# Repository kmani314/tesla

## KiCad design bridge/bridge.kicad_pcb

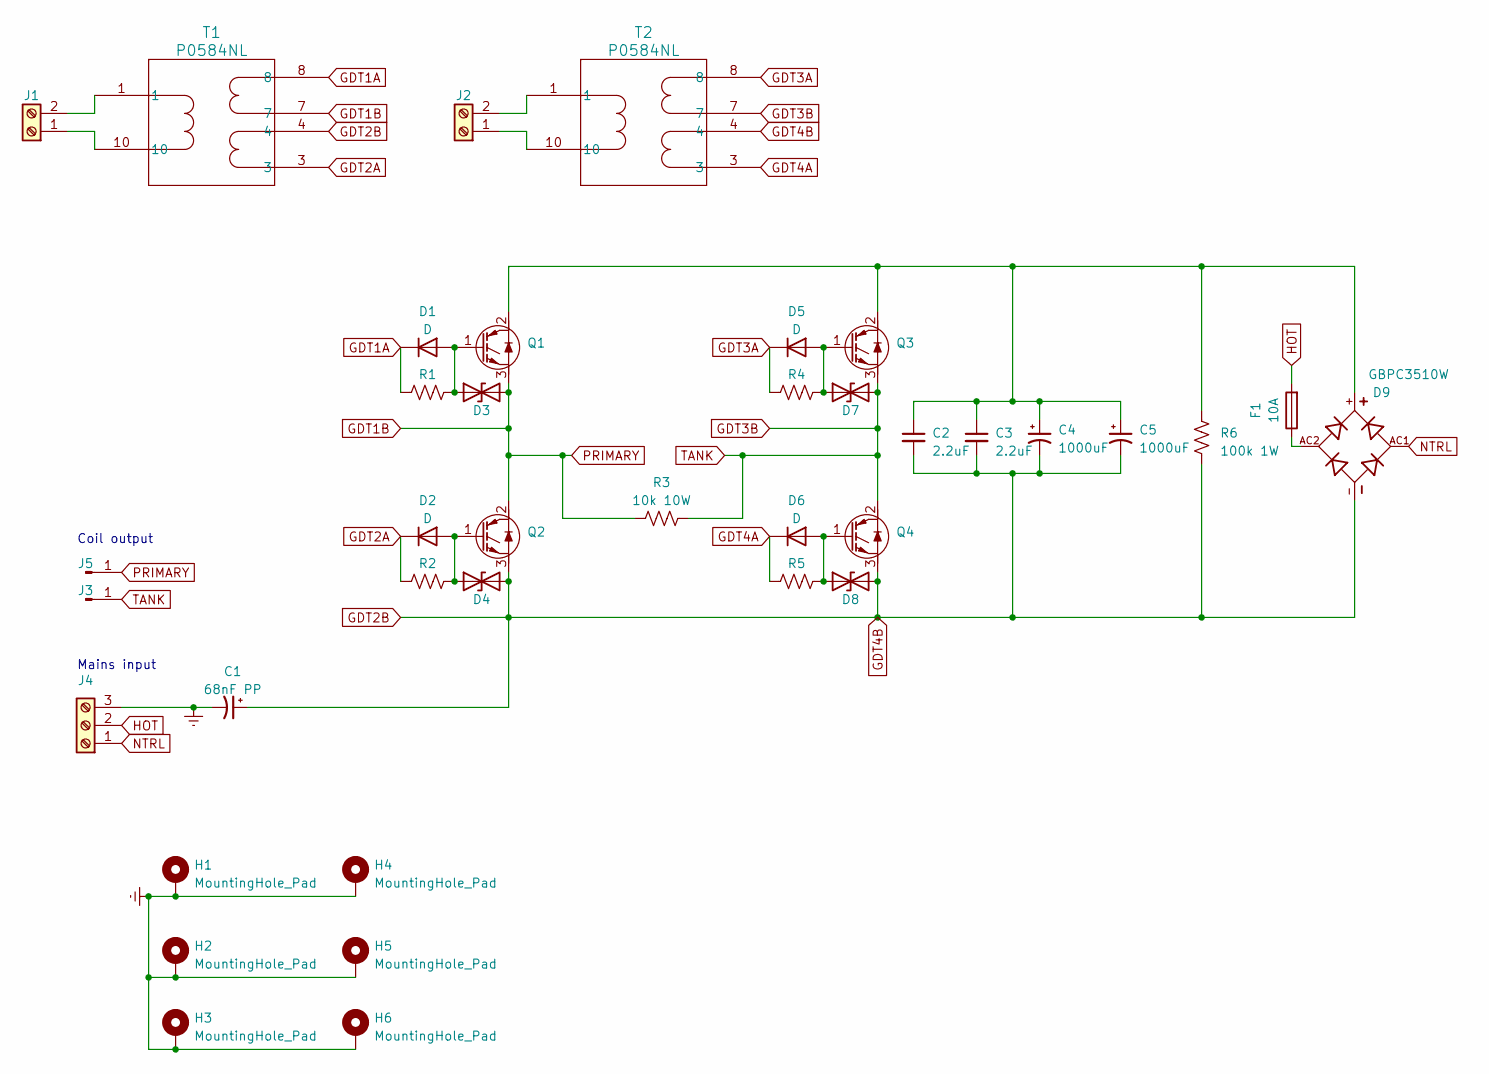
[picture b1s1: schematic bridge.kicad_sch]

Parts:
C1: 68nF PP; C_Rect_L18.0mm_W9.0mm_P15.00mm_FKS3_FKP3
C2, C3: 2.2uF; C_Rect_L26.5mm_W11.5mm_P22.50mm_MKS4
C4, C5: 1000uF; CP_Radial_D35.0mm_P10.00mm_SnapIn
D1, D2, D5, D6: D; D_SOD-123F
D3, D4, D7, D8: D_TVS; D_SMA
D9: GBPC3510W; DIOB_GBPC3510W; PARTREV L2103
F1: 10A; 696108003002
H1, H2, H3, H4, H5, H6: MountingHole_Pad; MountingHole_3.2mm_M3_Pad_Via
J1, J2: Screw_Terminal_01x02; PHOENIX_1935161
J3, J5: Conn_01x01_Pin; TE_1217861-1
J4: Screw_Terminal_01x03; PHOENIX_1935174
Q1, Q2, Q3, Q4: STGP7NC60HD; TO-3P-3_Horizontal_TabDown
R1, R2, R4, R5: R_US; R_1206_3216Metric_Pad1.30x1.75mm_HandSolder
R3: 10k 10W; R_Axial_Shunt_L22.2mm_W8.0mm_PS14.30mm_P25.40mm
R6: 100k 1W; R_Axial_DIN0207_L6.3mm_D2.5mm_P7.62mm_Horizontal
T1, T2: P0584NL; P0584NL_PUL

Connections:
Earth: C1.2, H1.1, H2.1, H3.1, H4.1, H5.1, H6.1, J4.3
GDT1A: D1.1 (K), R1.2, T1.8
GDT1B: D3.2 (A2), J5.1, Q1.3 (E), Q2.2 (C), R3.2, T1.7
GDT2A: D2.1 (K), R2.2, T1.3
GDT2B: C1.1, C2.2, C3.2, C4.2, C5.2, D4.2 (A2), D8.2 (A2), D9.-, Q2.3 (E), Q4.3 (E), R6.2, T1.4, T2.4
GDT3A: D5.1 (K), R4.2, T2.8
GDT3B: D7.2 (A2), J3.1, Q3.3 (E), Q4.2 (C), R3.1, T2.7
GDT4A: D6.1 (K), R5.2, T2.3
HOT: F1.2, J4.2
NTRL: D9.AC1, J4.1
unnamed: D1.2 (A), D3.1 (A1), Q1.1 (G), R1.1
unnamed: D2.2 (A), D4.1 (A1), Q2.1 (G), R2.1
unnamed: D5.2 (A), D7.1 (A1), Q3.1 (G), R4.1
unnamed: D6.2 (A), D8.1 (A1), Q4.1 (G), R5.1
unnamed: D9.AC2, F1.1
unnamed: J1.1, T1.10
unnamed: J1.2, T1.1
unnamed: J2.1, T2.10
unnamed: J2.2, T2.1
unnamed: C2.1, C3.1, C4.1, C5.1, D9.+, Q1.2 (C), Q3.2 (C), R6.1

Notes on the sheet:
Mains input
Coil output

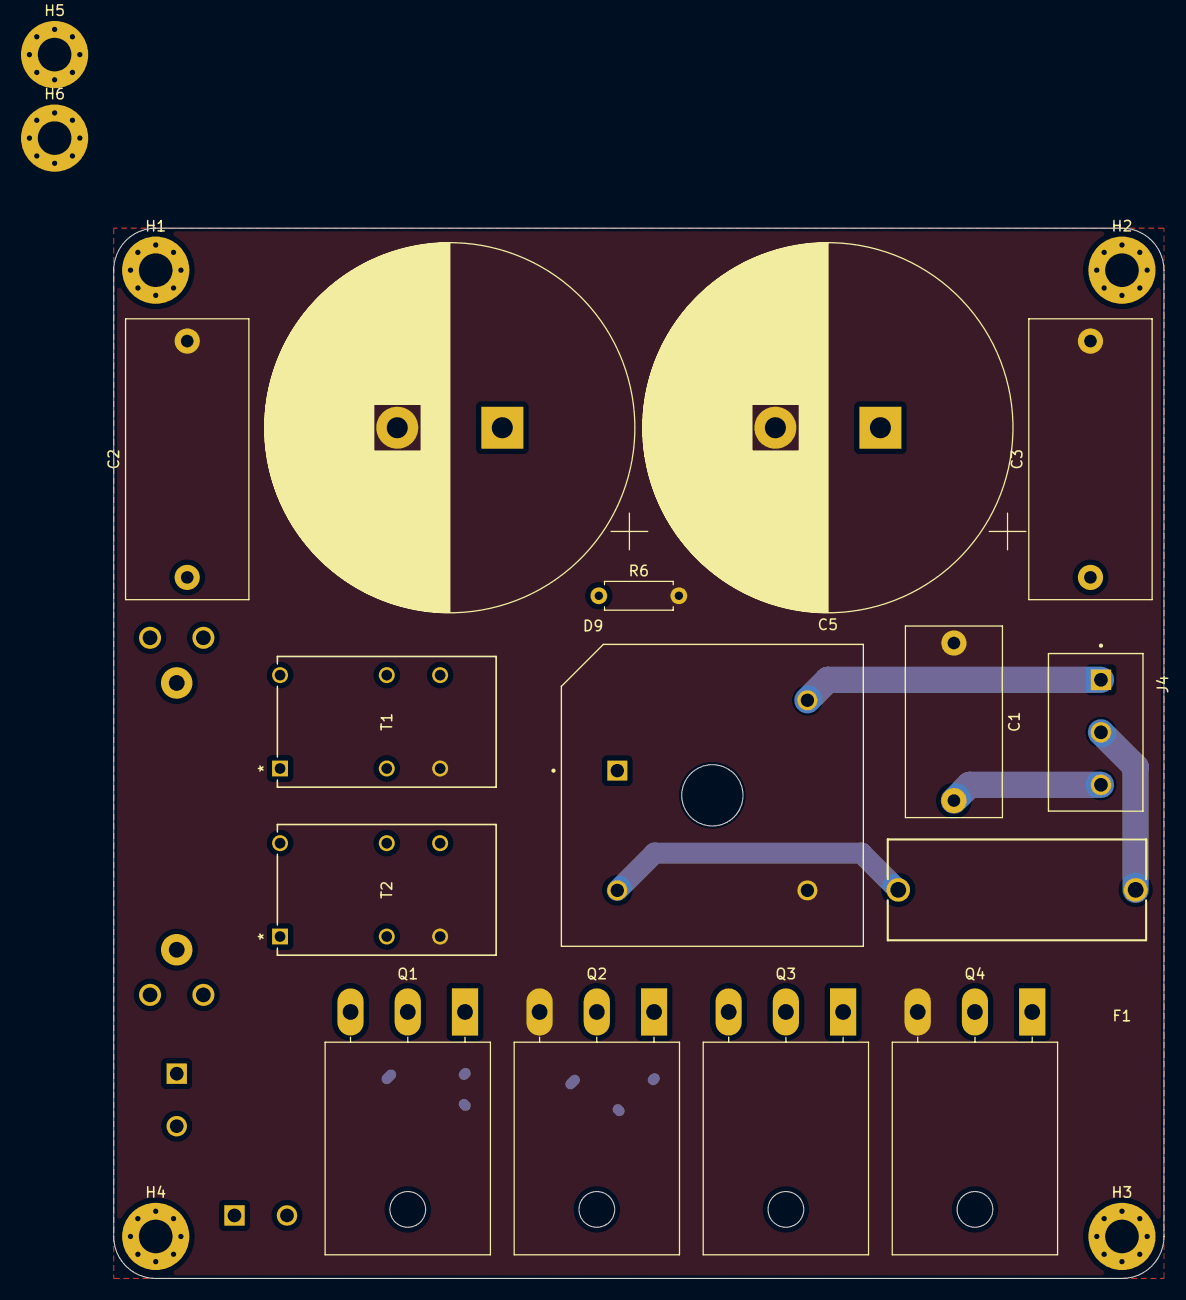
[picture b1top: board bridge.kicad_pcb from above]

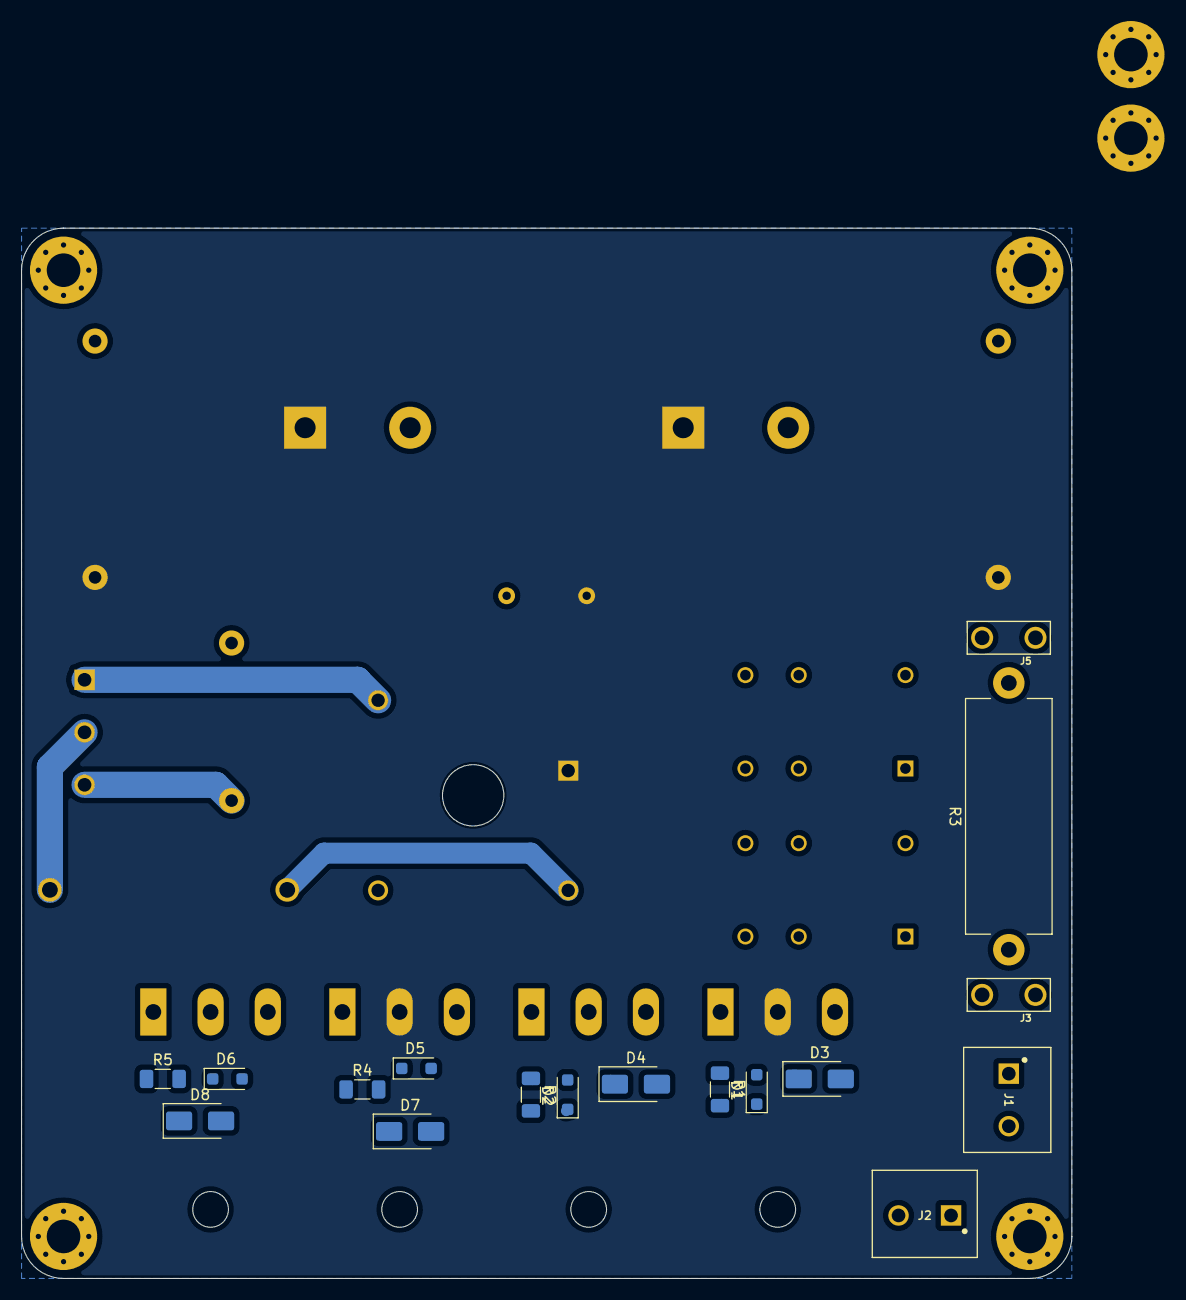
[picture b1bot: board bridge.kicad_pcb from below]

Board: 2 copper layers, 100.0 x 100.0 mm, 38 parts (17 on the bottom side), 20 nets.

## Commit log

2023-05-25 GDT driver done, figuring out interrupter and feedback mechanism
2023-05-26 prelim driver sch done
2023-05-26 cleanup files and fix gitignore autosaves
2023-05-27 finish basic bridge, remove voltage doubler
2023-05-28 bridge footprints done
2023-05-30 fix bridge, still figuring out layout
